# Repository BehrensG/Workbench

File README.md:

# Workbench
A workbench for testing and validating circuit designs.

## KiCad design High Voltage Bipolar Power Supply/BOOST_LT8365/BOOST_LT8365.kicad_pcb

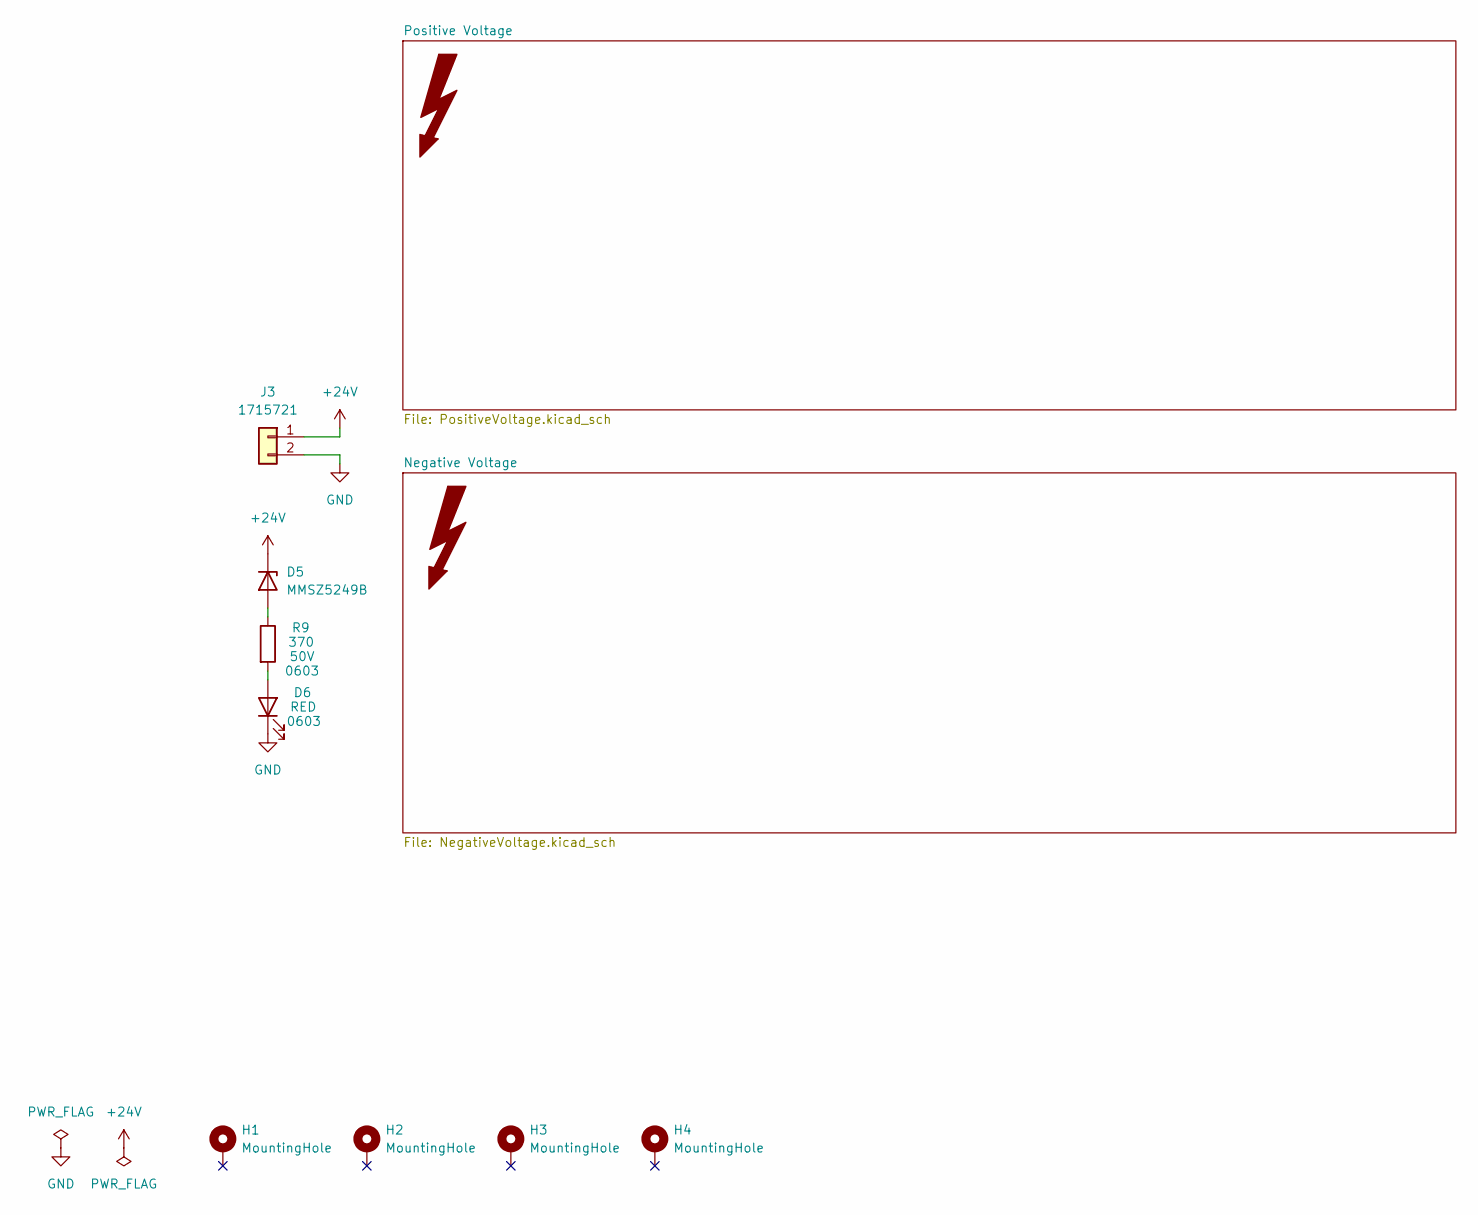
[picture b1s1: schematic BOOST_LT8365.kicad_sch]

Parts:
D5: MMSZ5249B; D_SOD-123
D6: RED; LED_0603_1608Metric_Pad1.05x0.95mm_HandSolder
H1, H2, H3, H4: MountingHole; MountingHole_3.2mm_M3_DIN965_Pad
J3: 1715721; TerminalBlock_Phoenix_MKDS-1,5-2_1x02_P5.00mm_Horizontal
R9: 370; R_0603_1608Metric_Pad0.98x0.95mm_HandSolder; Voltage 50V
SYM1, SYM2: SYM_Flash_XLarge; Symbol_HighVoltage_Triangle_8x7mm_Copper

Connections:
+24V: D5.1 (K), J3.1; also elsewhere on the board
GND: D6.1 (K), J3.2; also elsewhere on the board
unnamed: D5.2 (A), R9.1
unnamed: D6.2 (A), R9.2

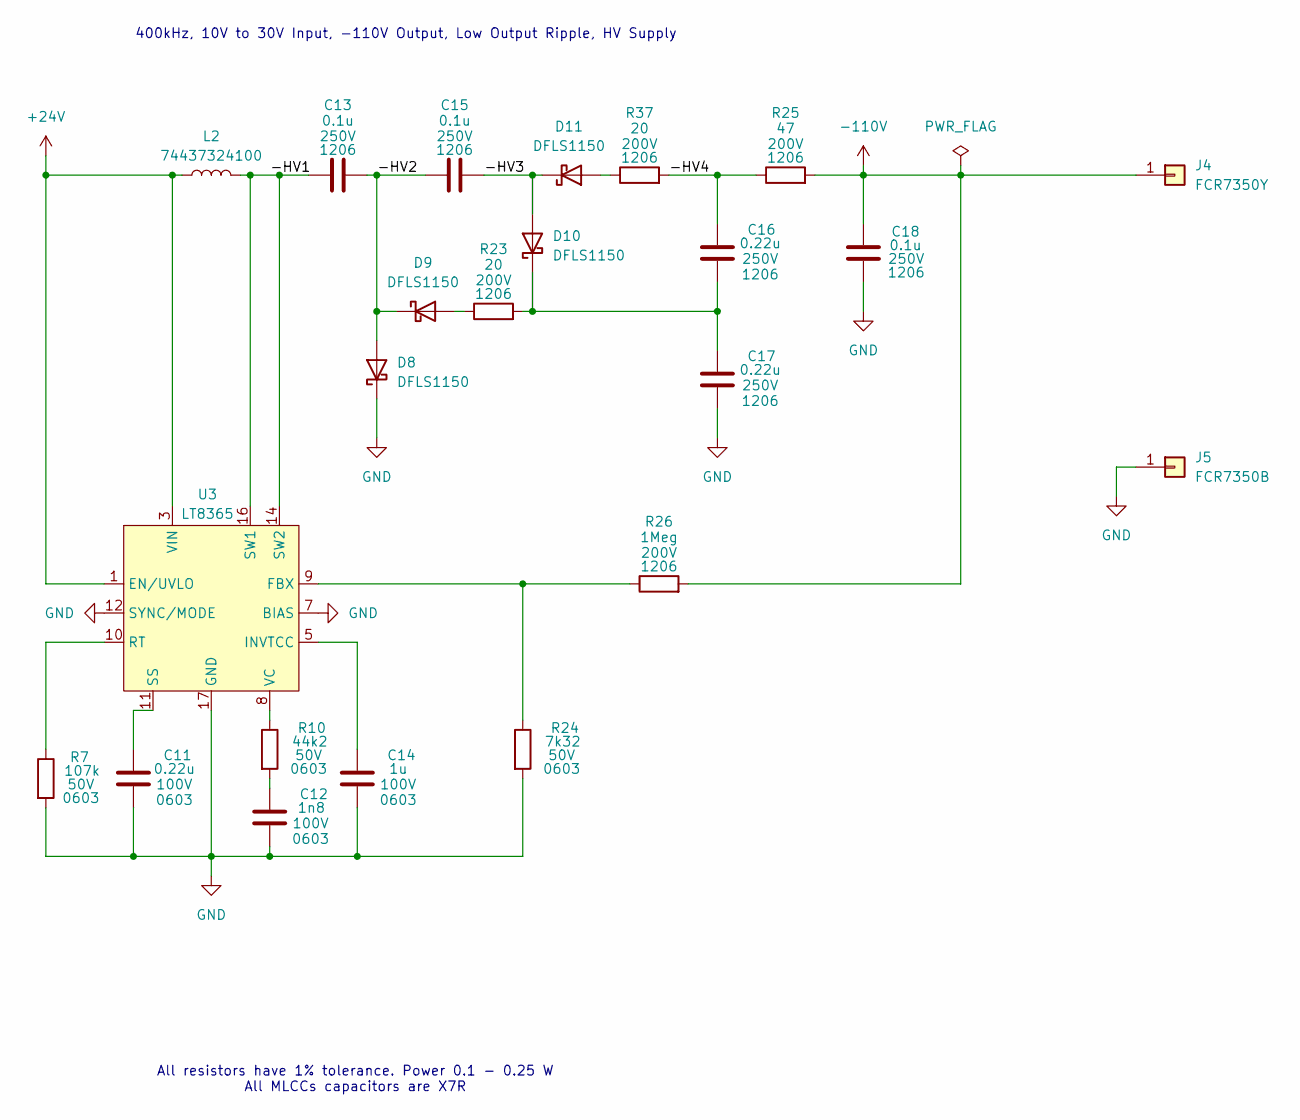
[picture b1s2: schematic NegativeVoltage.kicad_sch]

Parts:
C11: 0.22u; C_0603_1608Metric_Pad1.08x0.95mm_HandSolder; Voltage 100V
C12: 1n8; C_0603_1608Metric_Pad1.08x0.95mm_HandSolder; Voltage 100V
C13, C15, C18: 0.1u; C_1206_3216Metric_Pad1.33x1.80mm_HandSolder; Voltage 250V
C14: 1u; C_0603_1608Metric_Pad1.08x0.95mm_HandSolder; Voltage 100V
C16, C17: 0.22u; C_1206_3216Metric_Pad1.33x1.80mm_HandSolder; Voltage 250V
D8, D9, D10, D11: DFLS1150; D_PowerDI-123
J4: FCR7350Y; S16N-PC
J5: FCR7350B; S16N-PC
L2: 74437324100
R7: 107k; R_0603_1608Metric_Pad0.98x0.95mm_HandSolder; Voltage 50V
R10: 44k2; R_0603_1608Metric_Pad0.98x0.95mm_HandSolder; Voltage 50V
R23, R37: 20; R_1206_3216Metric_Pad1.30x1.75mm_HandSolder; Voltage 200V
R24: 7k32; R_0603_1608Metric_Pad0.98x0.95mm_HandSolder; Voltage 50V
R25: 47; R_1206_3216Metric_Pad1.30x1.75mm_HandSolder; Voltage 200V
R26: 1Meg; R_1206_3216Metric_Pad1.30x1.75mm_HandSolder; Voltage 200V
U3: LT8365; 05-08-1871_ADI

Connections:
+24V: L2.1, U3.1 (EN/UVLO), U3.3 (VIN); also elsewhere on the board
-110V: C18.1, J4.1, R25.2, R26.2
/Negative Voltage/-HV1: C13.1, L2.2, U3.14 (SW2), U3.16 (SW1)
/Negative Voltage/-HV2: C13.2, C15.1, D8.2 (A), D9.1 (K)
/Negative Voltage/-HV3: C15.2, D10.2 (A), D11.1 (K)
/Negative Voltage/-HV4: C16.1, R25.1, R37.2
GND: C11.2, C12.2, C14.2, C17.2, C18.2, D8.1 (K), J5.1, R7.2, R24.2, U3.7 (BIAS), U3.12 (SYNC/MODE), U3.17 (GND); also elsewhere on the board
unnamed: C12.1, R10.2
unnamed: D9.2 (A), R23.1
unnamed: C16.2, C17.1, D10.1 (K), R23.2
unnamed: D11.2 (A), R37.1
unnamed: R24.1, R26.1, U3.9 (FBX)
unnamed: C14.1, U3.5 (INVTCC)
unnamed: R7.1, U3.10 (RT)
unnamed: C11.1, U3.11 (SS)
unnamed: R10.1, U3.8 (VC)

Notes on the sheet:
All resistors have 1% tolerance. Power 0.1 - 0.25 W All MLCCs capacitors are X7R
400kHz, 10V to 30V Input, -110V Output, Low Output Ripple, HV Supply

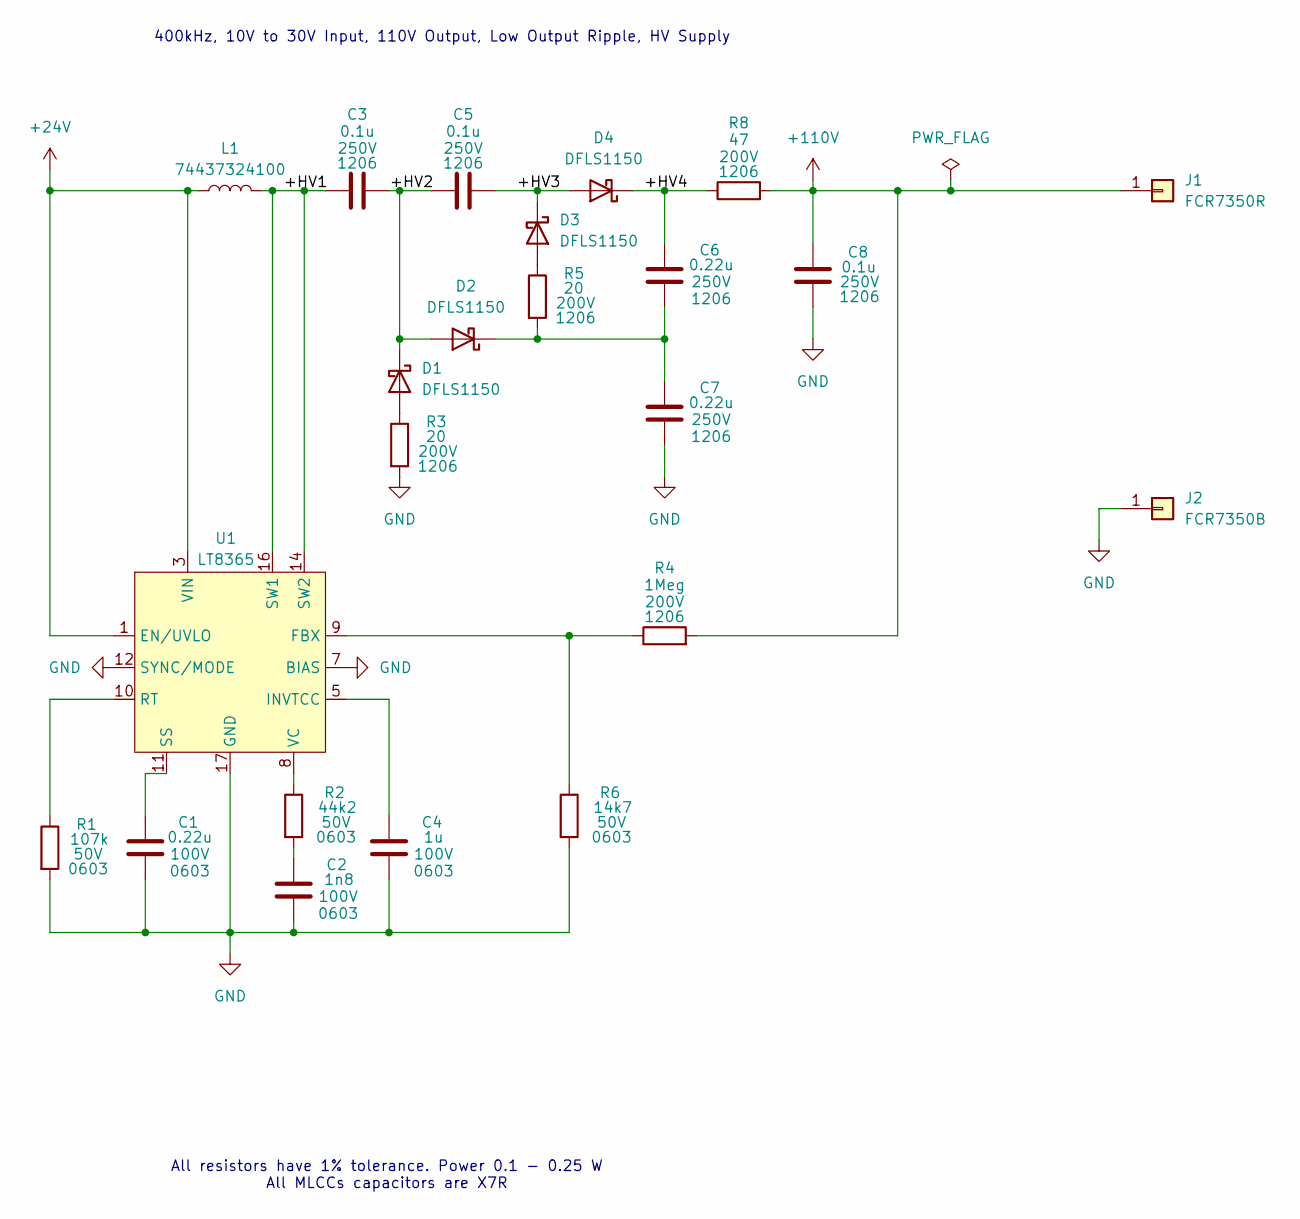
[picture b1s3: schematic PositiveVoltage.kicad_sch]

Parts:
C1: 0.22u; C_0603_1608Metric_Pad1.08x0.95mm_HandSolder; Voltage 100V
C2: 1n8; C_0603_1608Metric_Pad1.08x0.95mm_HandSolder; Voltage 100V
C3, C5, C8: 0.1u; C_1206_3216Metric_Pad1.33x1.80mm_HandSolder; Voltage 250V
C4: 1u; C_0603_1608Metric_Pad1.08x0.95mm_HandSolder; Voltage 100V
C6, C7: 0.22u; C_1206_3216Metric_Pad1.33x1.80mm_HandSolder; Voltage 250V
D1, D2, D3, D4: DFLS1150; D_PowerDI-123
J1: FCR7350R; S16N-PC
J2: FCR7350B; S16N-PC
L1: 74437324100
R1: 107k; R_0603_1608Metric_Pad0.98x0.95mm_HandSolder; Voltage 50V
R2: 44k2; R_0603_1608Metric_Pad0.98x0.95mm_HandSolder; Voltage 50V
R3, R5: 20; R_1206_3216Metric_Pad1.30x1.75mm_HandSolder; Voltage 200V
R4: 1Meg; R_1206_3216Metric_Pad1.30x1.75mm_HandSolder; Voltage 200V
R6: 14k7; R_0603_1608Metric_Pad0.98x0.95mm_HandSolder; Voltage 50V
R8: 47; R_1206_3216Metric_Pad1.30x1.75mm_HandSolder; Voltage 200V
U1: LT8365; 05-08-1871_ADI

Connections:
+24V: L1.1, U1.1 (EN/UVLO), U1.3 (VIN); also elsewhere on the board
+110V: C8.1, J1.1, R4.2, R8.2
/Positive Voltage/+HV1: C3.1, L1.2, U1.14 (SW2), U1.16 (SW1)
/Positive Voltage/+HV2: C3.2, C5.1, D1.1 (K), D2.2 (A)
/Positive Voltage/+HV3: C5.2, D3.1 (K), D4.2 (A)
/Positive Voltage/+HV4: C6.1, D4.1 (K), R8.1
GND: C1.2, C2.2, C4.2, C7.2, C8.2, J2.1, R1.2, R3.2, R6.2, U1.7 (BIAS), U1.12 (SYNC/MODE), U1.17 (GND); also elsewhere on the board
unnamed: C2.1, R2.2
unnamed: D1.2 (A), R3.1
unnamed: C6.2, C7.1, D2.1 (K), R5.2
unnamed: D3.2 (A), R5.1
unnamed: R4.1, R6.1, U1.9 (FBX)
unnamed: C4.1, U1.5 (INVTCC)
unnamed: R1.1, U1.10 (RT)
unnamed: C1.1, U1.11 (SS)
unnamed: R2.1, U1.8 (VC)

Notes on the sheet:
All resistors have 1% tolerance. Power 0.1 - 0.25 W All MLCCs capacitors are X7R
400kHz, 10V to 30V Input, 110V Output, Low Output Ripple, HV Supply

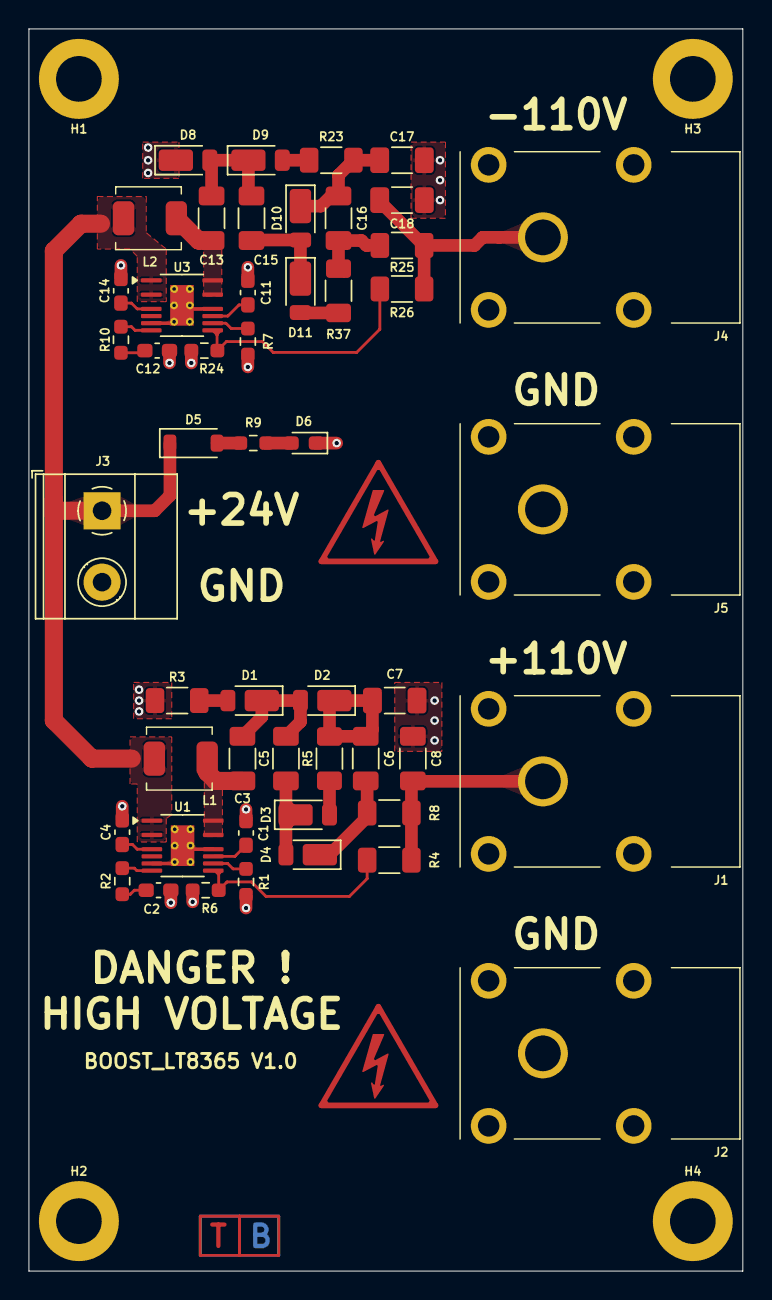
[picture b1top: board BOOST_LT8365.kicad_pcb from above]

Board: 2 copper layers, 50.0 x 87.0 mm, 56 parts (0 on the bottom side), 32 nets.

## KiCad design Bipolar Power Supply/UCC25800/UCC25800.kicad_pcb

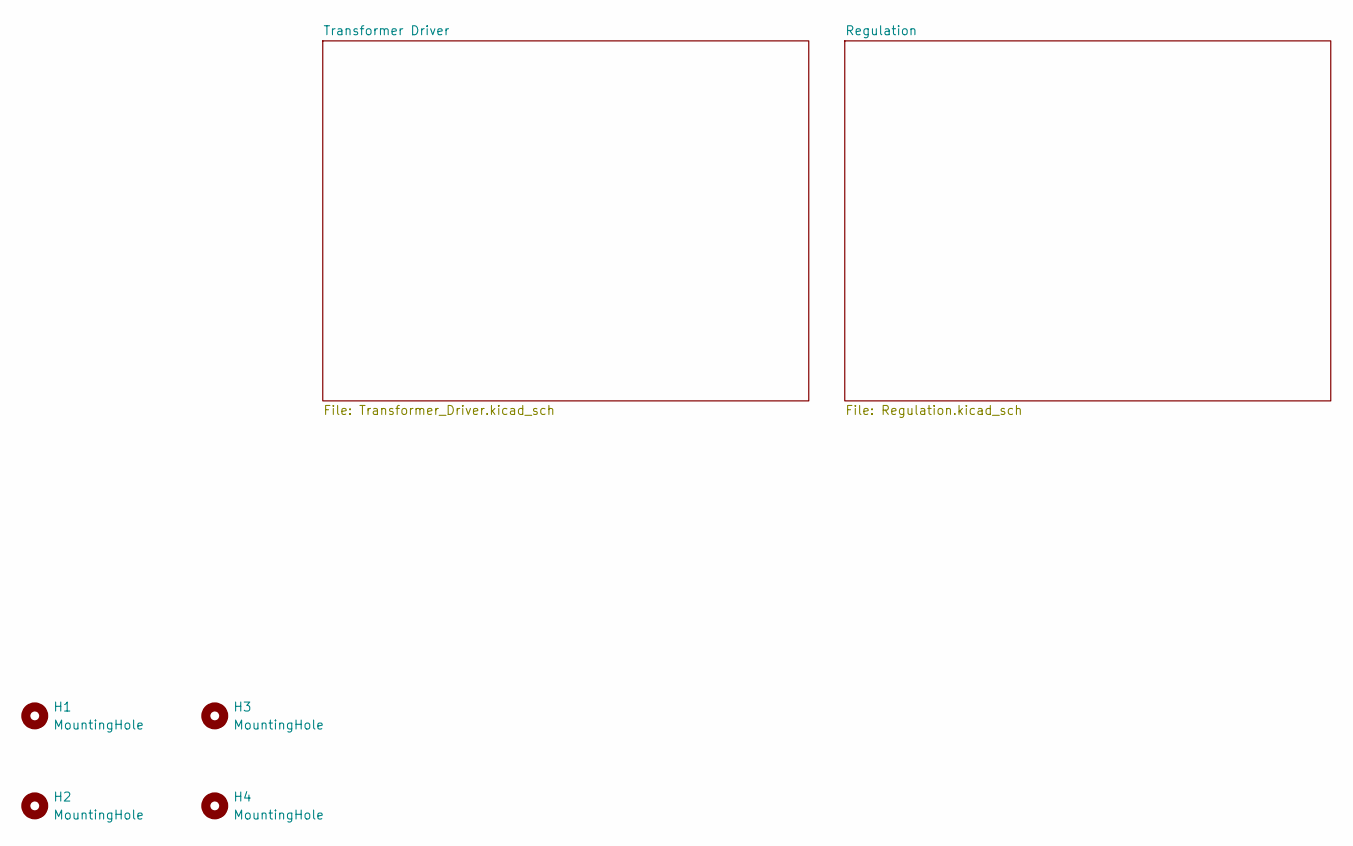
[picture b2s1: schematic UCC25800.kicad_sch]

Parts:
H1, H2, H3, H4: MountingHole; MountingHole_2.5mm

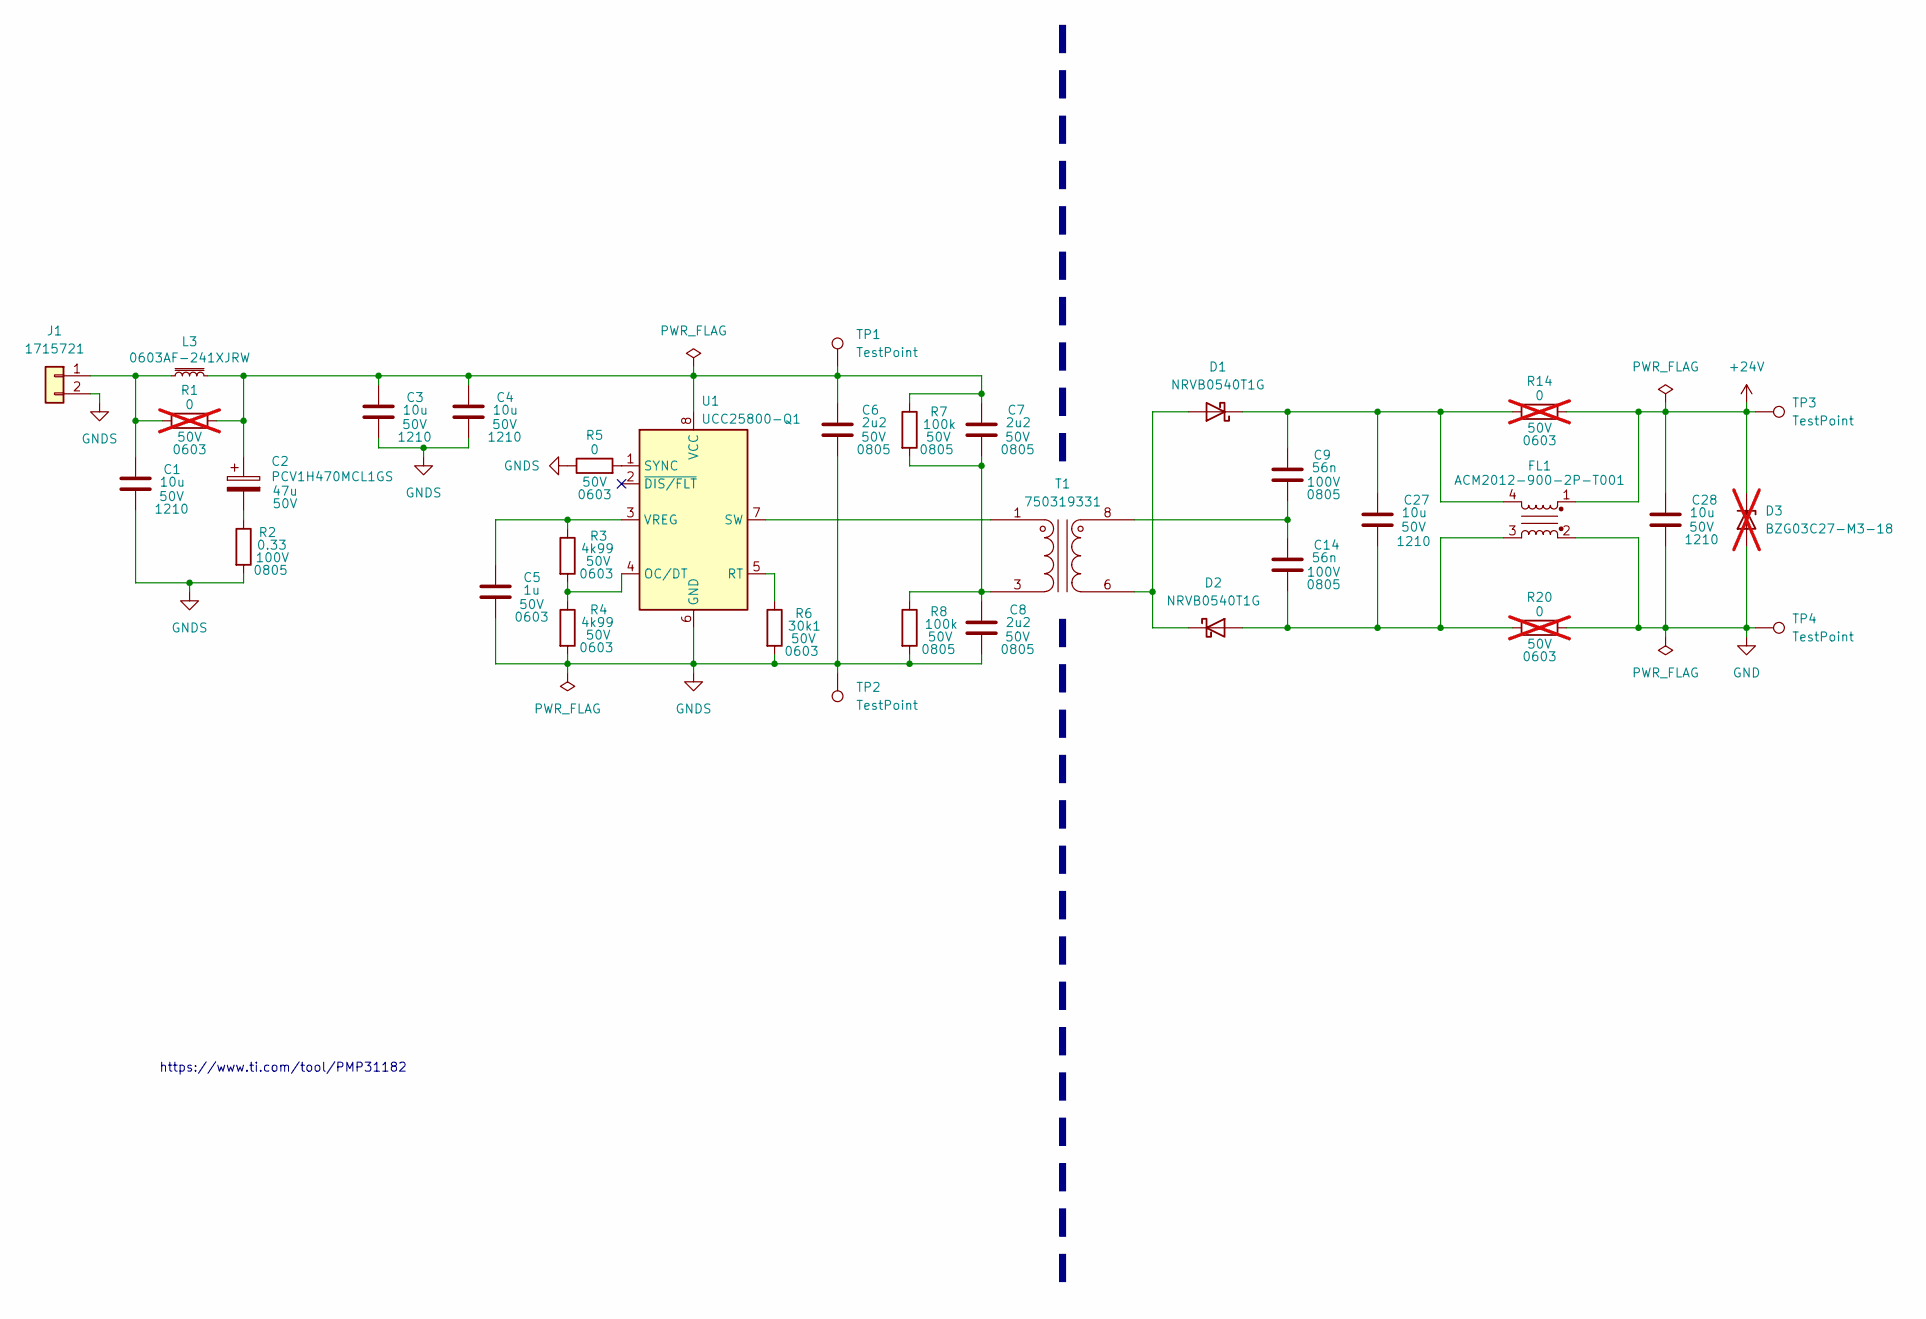
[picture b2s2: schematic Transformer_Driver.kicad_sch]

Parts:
C1, C3, C4, C27, C28: 10u; C_1210_3225Metric_Pad1.33x2.70mm_HandSolder; Voltage 50V
C2: PCV1H470MCL1GS; CP_Elec_10x10; Voltage 50V
C5: 1u; C_0603_1608Metric_Pad1.08x0.95mm_HandSolder; Voltage 50V
C6, C7, C8: 2u2; C_0805_2012Metric_Pad1.18x1.45mm_HandSolder; Voltage 50V
C9, C14: 56n; C_0805_2012Metric_Pad1.18x1.45mm_HandSolder; Voltage 100V
D1, D2: NRVB0540T1G; D_SOD-123
D3: BZG03C27-M3-18; D_SMA; not fitted
FL1: ACM2012-900-2P-T001
J1: 1715721; TerminalBlock_Phoenix_MKDS-1,5-2_1x02_P5.00mm_Horizontal
L3: 0603AF-241XJRW; 0603PS-SRF
R1, R14, R20: 0; R_0603_1608Metric_Pad0.98x0.95mm_HandSolder; Voltage 50V; not fitted
R2: 0.33; R_0805_2012Metric_Pad1.20x1.40mm_HandSolder; Voltage 100V
R3, R4: 4k99; R_0603_1608Metric_Pad0.98x0.95mm_HandSolder; Voltage 50V
R5: 0; R_0603_1608Metric_Pad0.98x0.95mm_HandSolder; Voltage 50V
R6: 30k1; R_0603_1608Metric_Pad0.98x0.95mm_HandSolder; Voltage 50V
R7, R8: 100k; R_0805_2012Metric_Pad1.20x1.40mm_HandSolder; Voltage 50V
T1: 750319331
TP1, TP2, TP3, TP4: TestPoint; TestPoint_Keystone_5005-5009_Compact
U1: UCC25800-Q1; HVSSOP-8-1EP_3x3mm_P0.65mm_EP1.57x1.89mm_ThermalVias

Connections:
+24V: C28.1, D3.1 (K), FL1.1, R14.2, TP3.1; also elsewhere on the board
GND: C28.2, D3.2 (A), FL1.2, R20.2, TP4.1; also elsewhere on the board
GNDS: C1.2, C3.2, C4.2, C5.2, C6.2, C8.2, J1.2, R2.2, R4.2, R5.1, R6.2, R8.2, TP2.1, U1.6 (GND), U1.9 (GND)
unnamed: C2.2, R2.1
unnamed: D1.2 (A), D2.1 (K), T1.6 (SA)
unnamed: C9.1, C27.1, D1.1 (K), FL1.4, R14.1
unnamed: C14.2, C27.2, D2.2 (A), FL1.3, R20.1
unnamed: C1.1, J1.1, L3.1, R1.1
unnamed: T1.1 (AA), U1.7 (SW)
unnamed: C7.2, C8.1, R7.2, R8.1, T1.3 (AB)
unnamed: C9.2, C14.1, T1.8 (SB)
unnamed: R3.2, R4.1, U1.4 (OC/DT)
unnamed: R6.1, U1.5 (RT)
unnamed: R5.2, U1.1 (SYNC)
unnamed: C2.1, C3.1, C4.1, C6.1, C7.1, L3.2, R1.2, R7.1, TP1.1, U1.8 (VCC)
unnamed: C5.1, R3.1, U1.3 (VREG)

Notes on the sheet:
https://www.ti.com/tool/PMP31182

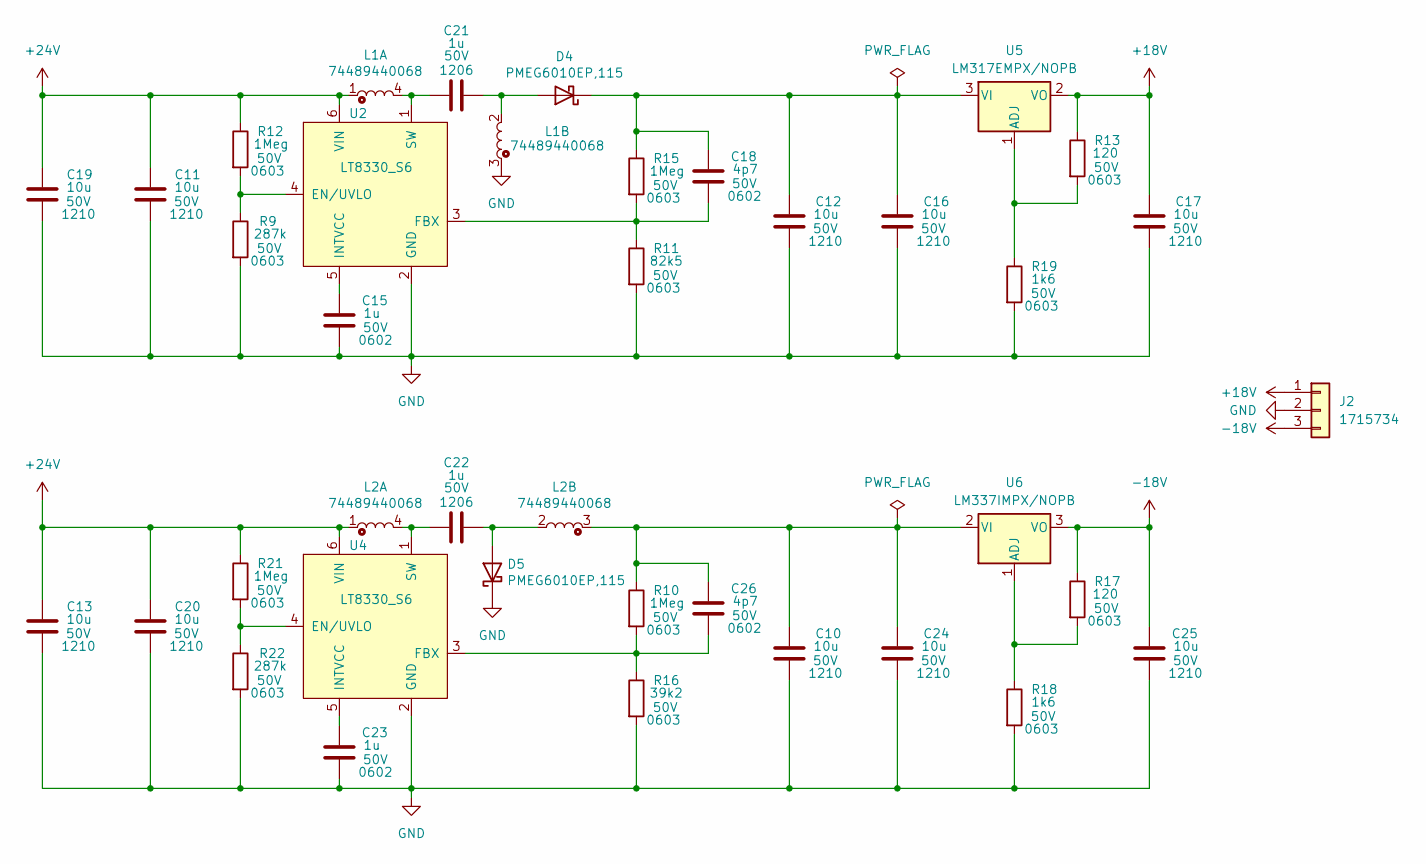
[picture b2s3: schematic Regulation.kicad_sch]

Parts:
C10, C11, C12, C13, C16, C17, C19, C20, C24, C25: 10u; C_1210_3225Metric_Pad1.33x2.70mm_HandSolder; Voltage 50V
C15, C23: 1u; C_0603_1608Metric_Pad1.08x0.95mm_HandSolder; Voltage 50V
C18, C26: 4p7; C_0603_1608Metric_Pad1.08x0.95mm_HandSolder; Voltage 50V
C21, C22: 1u; C_1206_3216Metric_Pad1.33x1.80mm_HandSolder; Voltage 50V
D4, D5: PMEG6010EP,115; D_SOD-128
J2: 1715734; TerminalBlock_Phoenix_MKDS-1,5-3-5.08_1x03_P5.08mm_Horizont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
L1, L2: 74489440068
R9, R22: 287k; R_0603_1608Metric_Pad0.98x0.95mm_HandSolder; Voltage 50V
R10, R12, R15, R21: 1Meg; R_0603_1608Metric_Pad0.98x0.95mm_HandSolder; Voltage 50V
R11: 82k5; R_0603_1608Metric_Pad0.98x0.95mm_HandSolder; Voltage 50V
R13, R17: 120; R_0603_1608Metric_Pad0.98x0.95mm_HandSolder; Voltage 50V
R16: 39k2; R_0603_1608Metric_Pad0.98x0.95mm_HandSolder; Voltage 50V
R18, R19: 1k6; R_0603_1608Metric_Pad0.98x0.95mm_HandSolder; Voltage 50V
U2, U4: LT8330_S6; TSOT-23-6_HandSoldering
U5: LM317EMPX/NOPB; SOT-223-3_TabPin2
U6: LM337IMPX/NOPB; SOT-223-3_TabPin2

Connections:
+18V: C17.1, J2.1, R13.1, U5.2 (VO)
+24V: C11.1, C13.1, C19.1, C20.1, L1.1, L2.1, R12.1, R21.1, U2.6 (VIN), U4.6 (VIN); also elsewhere on the board
-18V: C25.1, J2.3, R17.1, U6.3 (VO)
GND: C10.2, C11.2, C12.2, C13.2, C15.2, C16.2, C17.2, C19.2, C20.2, C23.2, C24.2, C25.2, D5.1 (K), J2.2, L1.3, R9.2, R11.2, R16.2, R18.2, R19.2, R22.2, U2.2 (GND), U4.2 (GND); also elsewhere on the board
unnamed: C21.1, D4.2 (A), L1.2
unnamed: C12.1, C16.1, C18.1, D4.1 (K), R15.1, U5.3 (VI)
unnamed: C22.1, D5.2 (A), L2.2
unnamed: R9.1, R12.2, U2.4 (EN/UVLO)
unnamed: C18.2, R11.1, R15.2, U2.3 (FBX)
unnamed: C15.1, U2.5 (INTVCC)
unnamed: C21.2, L1.4, U2.1 (SW)
unnamed: R21.2, R22.1, U4.4 (EN/UVLO)
unnamed: C26.2, R10.2, R16.1, U4.3 (FBX)
unnamed: C23.1, U4.5 (INTVCC)
unnamed: C22.2, L2.4, U4.1 (SW)
unnamed: R13.2, R19.1, U5.1 (ADJ)
unnamed: R17.2, R18.1, U6.1 (ADJ)
unnamed: C10.1, C24.1, C26.1, L2.3, R10.1, U6.2 (VI)

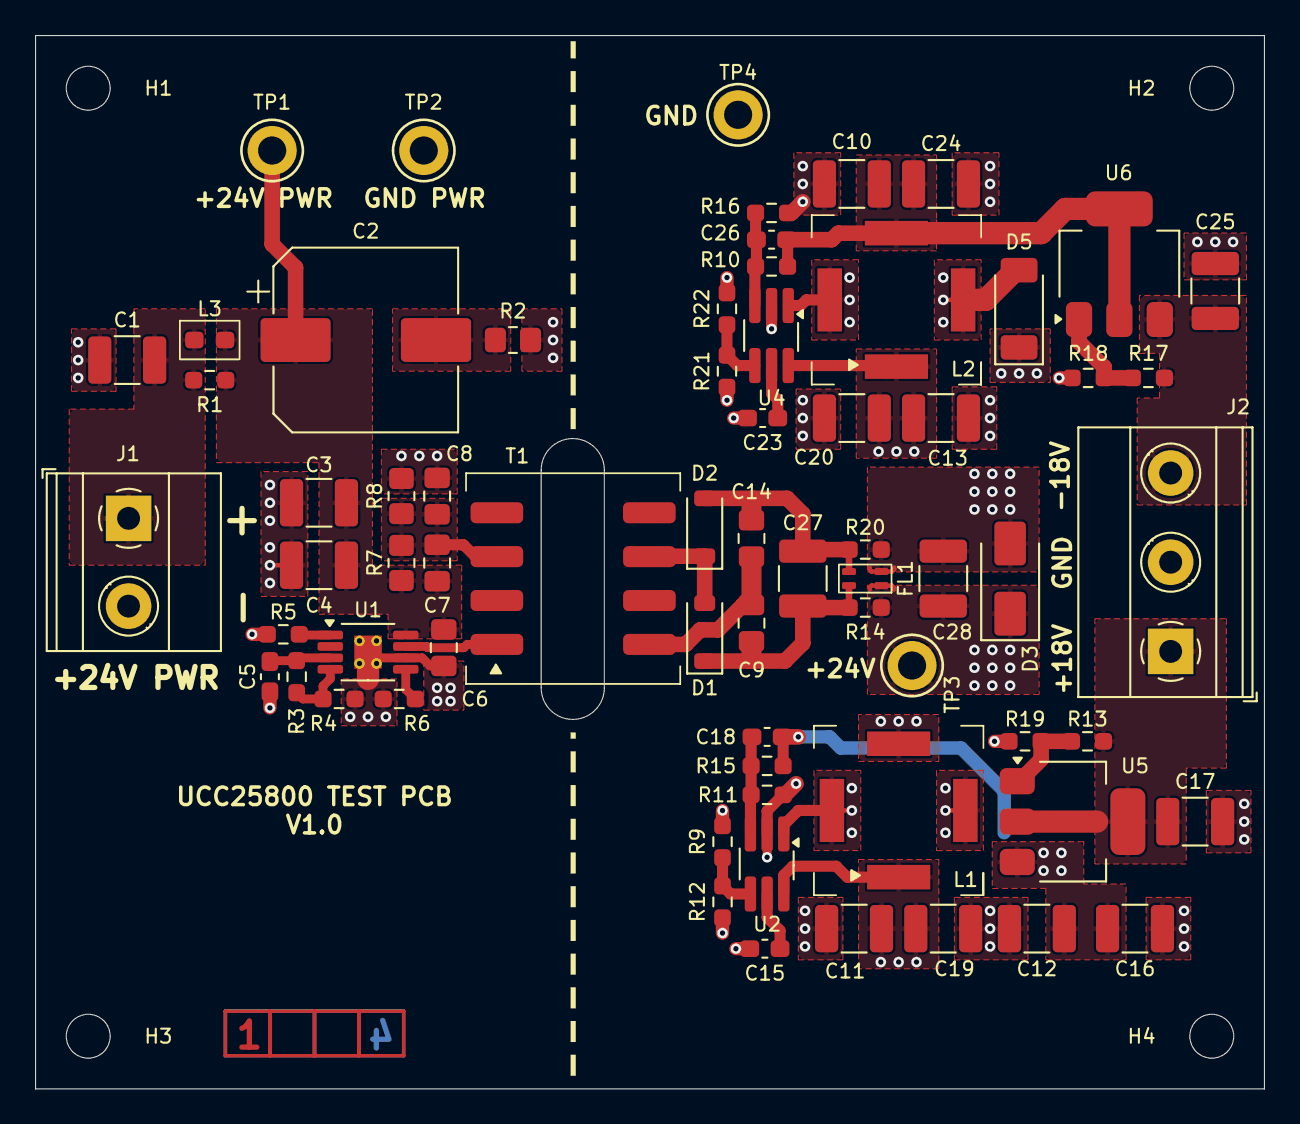
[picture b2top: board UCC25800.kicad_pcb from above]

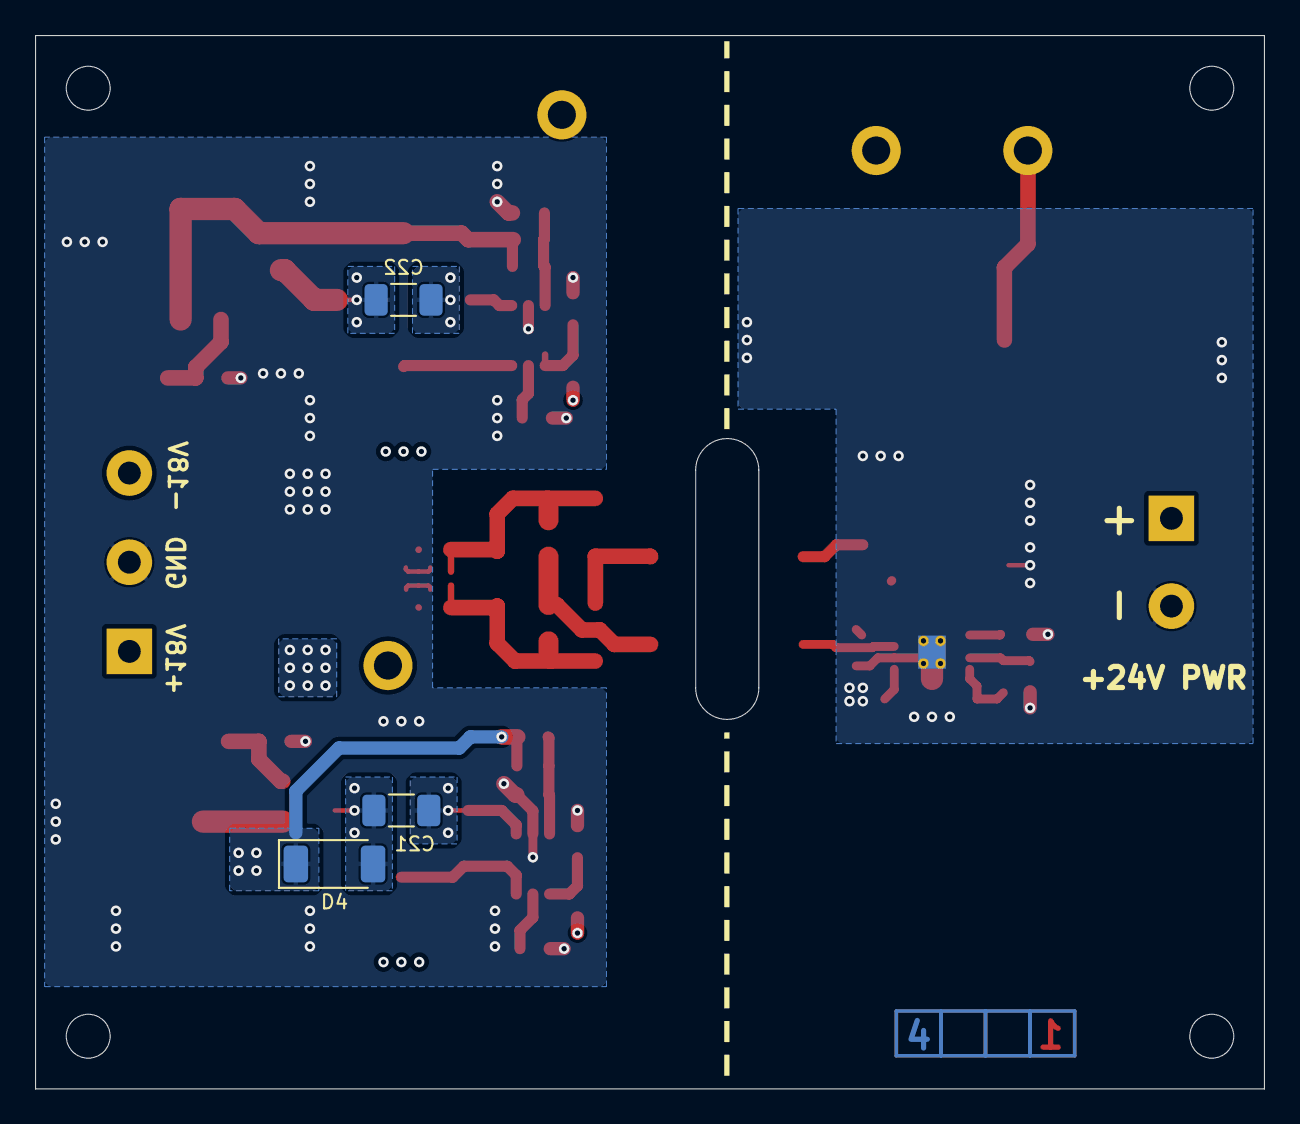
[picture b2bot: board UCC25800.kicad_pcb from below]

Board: 4 copper layers, 70.0 x 60.0 mm, 75 parts (3 on the bottom side), 32 nets.

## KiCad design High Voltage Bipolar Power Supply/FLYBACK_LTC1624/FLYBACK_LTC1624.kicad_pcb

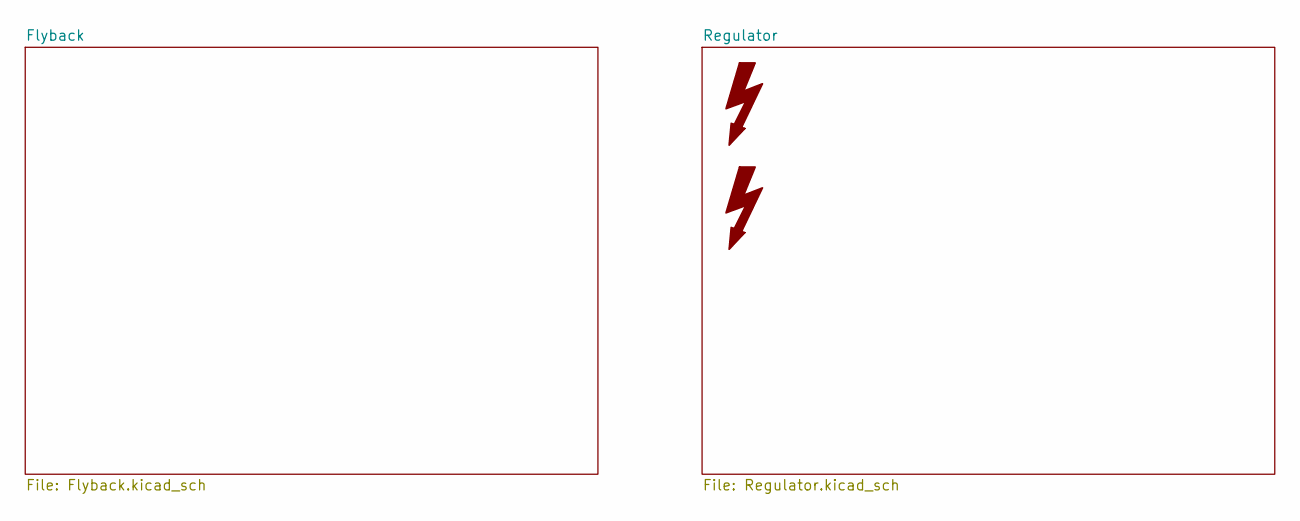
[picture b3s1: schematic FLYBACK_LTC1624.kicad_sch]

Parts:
SYM1: SYM_Flash_Large; Symbol_Attention_Triangle_8x7mm_Copper
SYM2: SYM_Flash_Large; Symbol_HighVoltage_Triangle_8x7mm_Copper
